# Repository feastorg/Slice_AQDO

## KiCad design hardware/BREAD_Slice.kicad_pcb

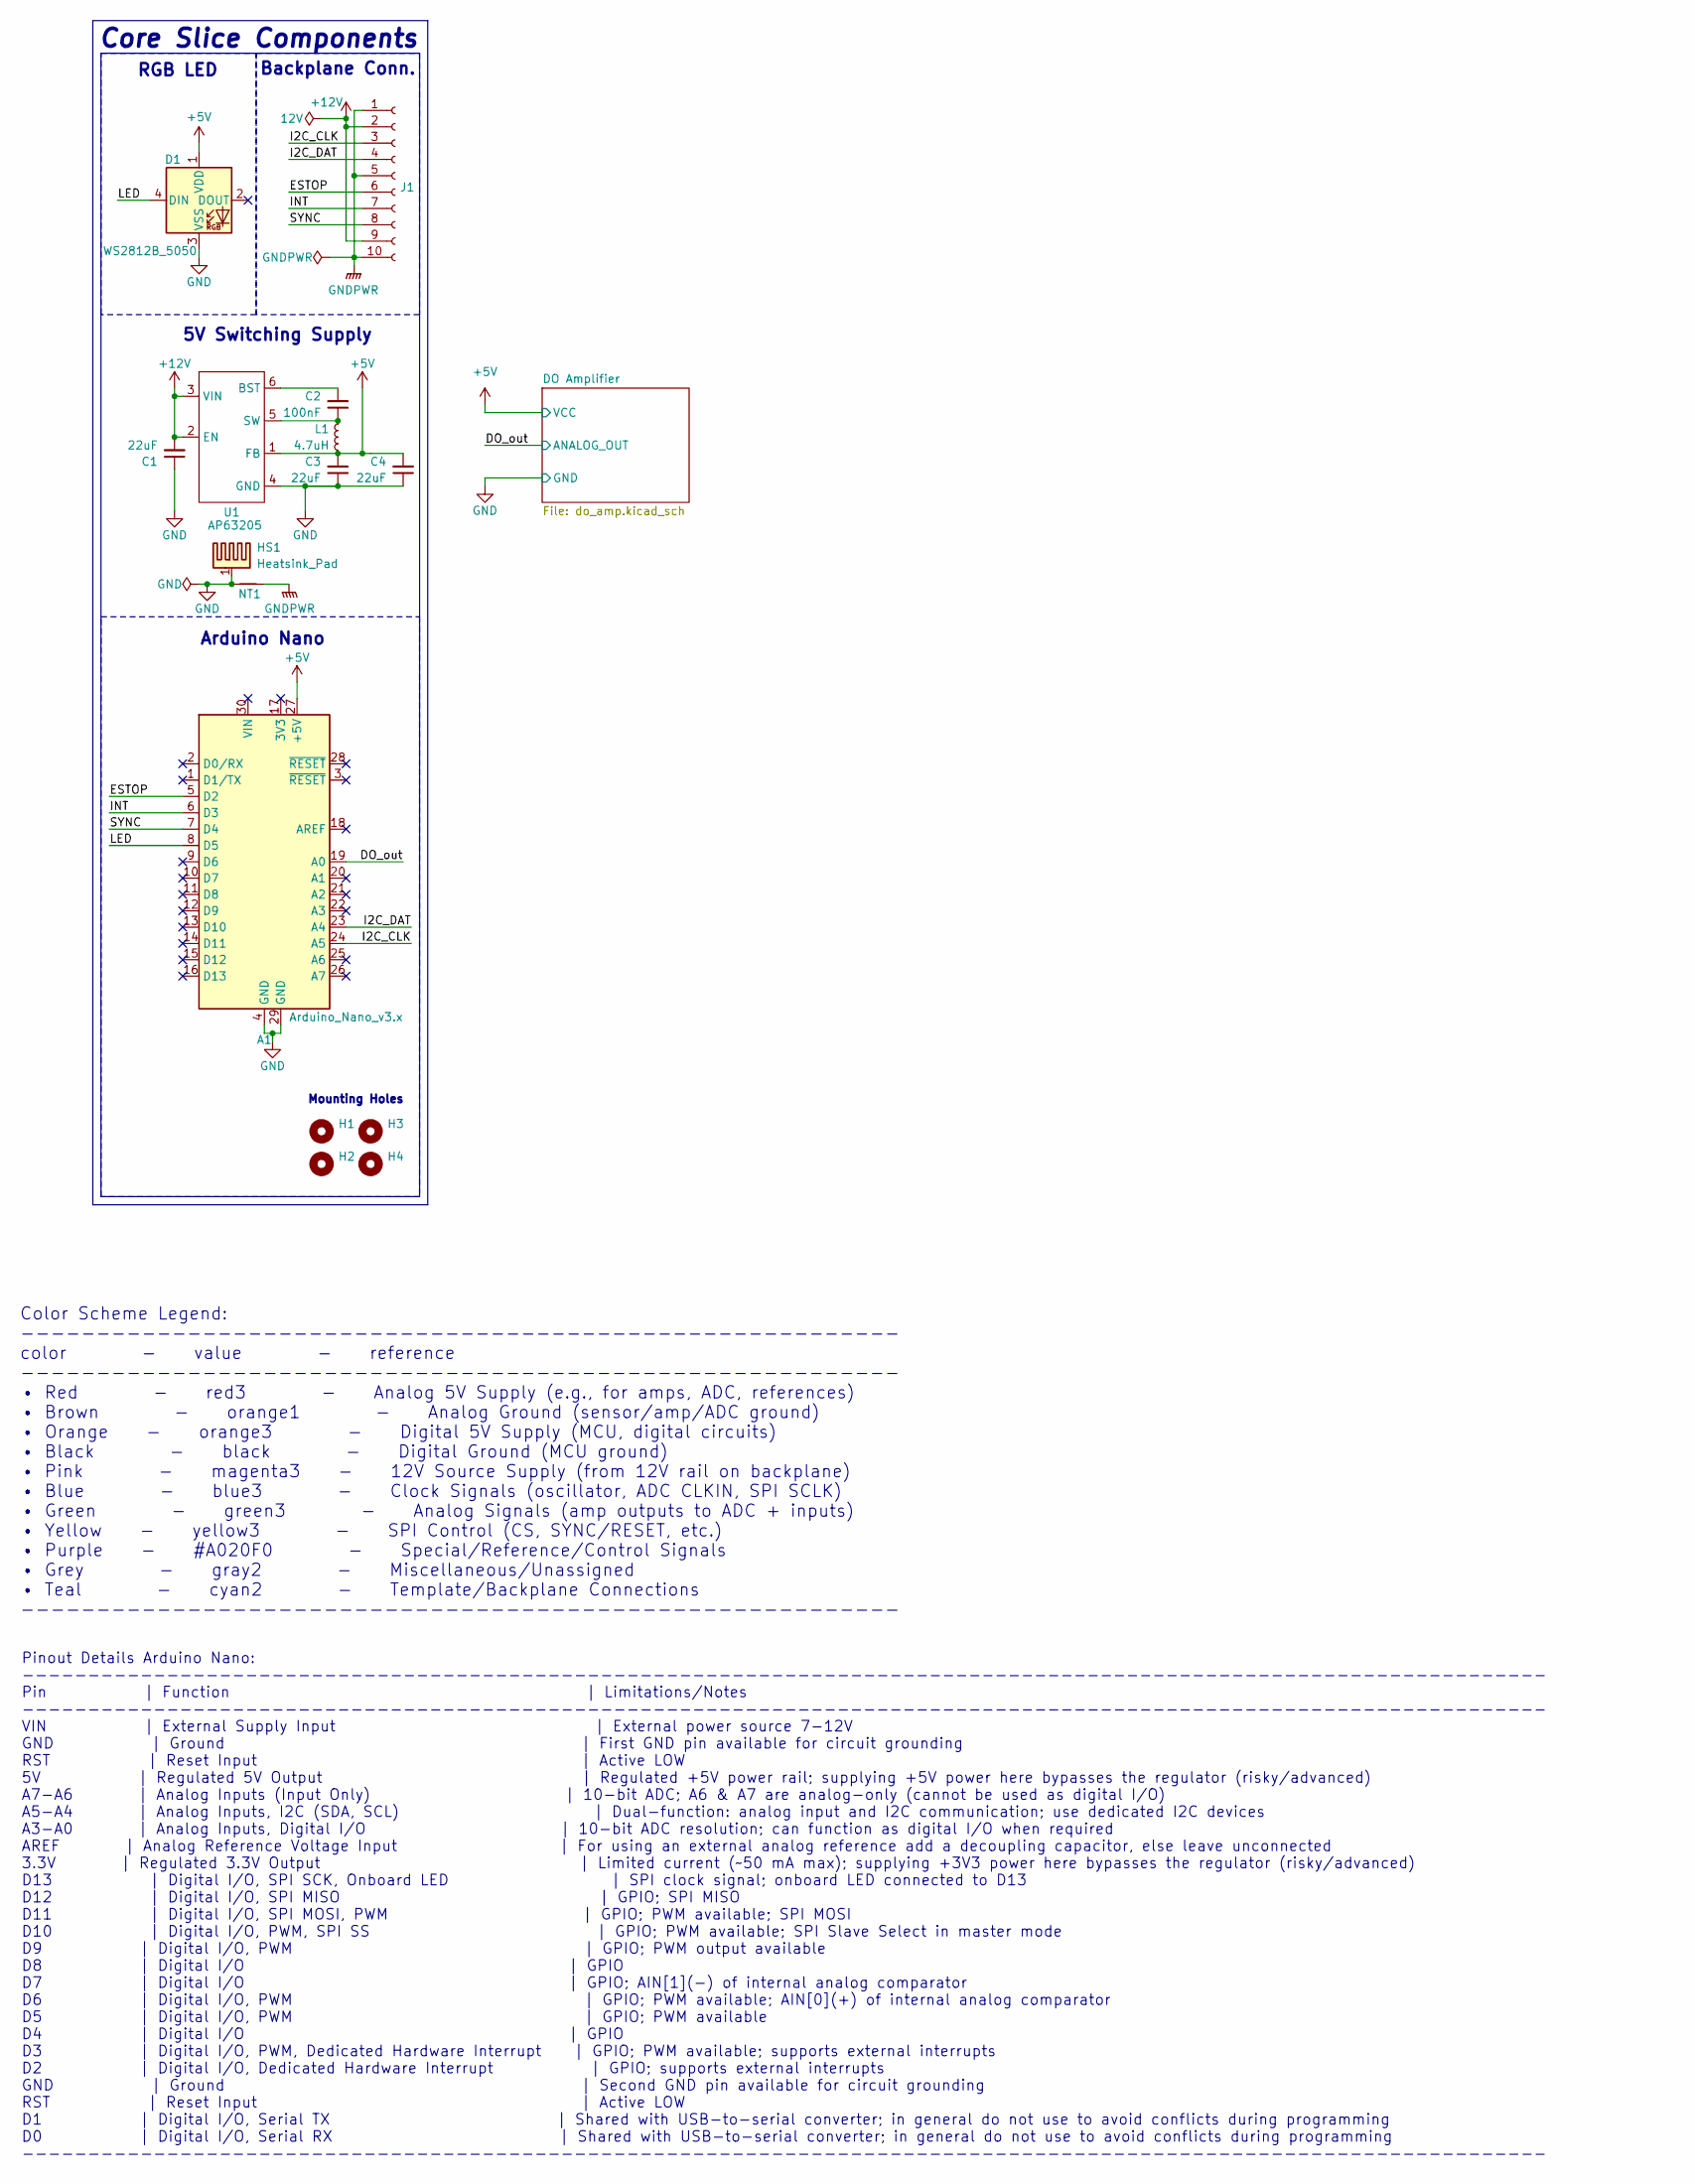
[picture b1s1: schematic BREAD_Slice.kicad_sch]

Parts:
A1: Arduino_Nano_v3.x; Arduino_Nano
C1, C3, C4: 22uF; C_1206_3216Metric
C2: 100nF; C_1206_3216Metric
D1: WS2812B_5050; WS2812-5050-4PIN
H1, H2, H3, H4: MountingHole; MountingHole_5mm
HS1: Heatsink_Pad; Thermal_Pad
J1: Conn_01x10_Female; PinSocket_1x10_P2.54mm_Horizontal
L1: 4.7uH; L_1210_3225Metric
NT1: NetTie_2; NetTie-2_SMD_Pad2.0mm
U1: AP63205; TSOT-23-6

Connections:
+5V: A1.27 (+5V), C3.2, C4.2, D1.1 (VDD), L1.2, U1.1 (FB); also elsewhere on the board
+12V: C1.2, J1.2, J1.9, U1.2 (EN), U1.3 (VIN)
/DO_out: A1.19 (A0); also elsewhere on the board
/ESTOP: A1.5 (D2), J1.6
/I2C_CLK: A1.24 (A5), J1.3
/I2C_DAT: A1.23 (A4), J1.4
/INT: A1.6 (D3), J1.7
/LED: A1.8 (D5), D1.4 (DIN)
/SYNC: A1.7 (D4), J1.8
GND: A1.4 (GND), A1.29 (GND), C1.1, C3.1, C4.1, D1.3 (VSS), HS1.1, NT1.1, U1.4 (GND); also elsewhere on the board
GNDPWR: J1.1, J1.5, J1.10, NT1.2
unnamed: C2.2, U1.6 (BST)
unnamed: C2.1, L1.1, U1.5 (SW)

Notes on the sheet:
5V Switching Supply
Pinout Details Arduino Nano: -------------------------------------------------------------------------------------------------------------------- Pin | Function | Limitations/Notes -------------------------------------------------------------------------------------------------------------------- V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
RGB LED
Color Scheme Legend: ---------------------------------------------------------- color - value - reference ---------------------------------------------------------- • Red - red3 - Analog 5V Supply (e.g., for amps, ADC, references) • Brown - orange1 - Analog Ground (sensor/amp/ADC ground) • Orange -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
Core Slice Components
Arduino Nano
Mounting Holes
Backplane Conn.

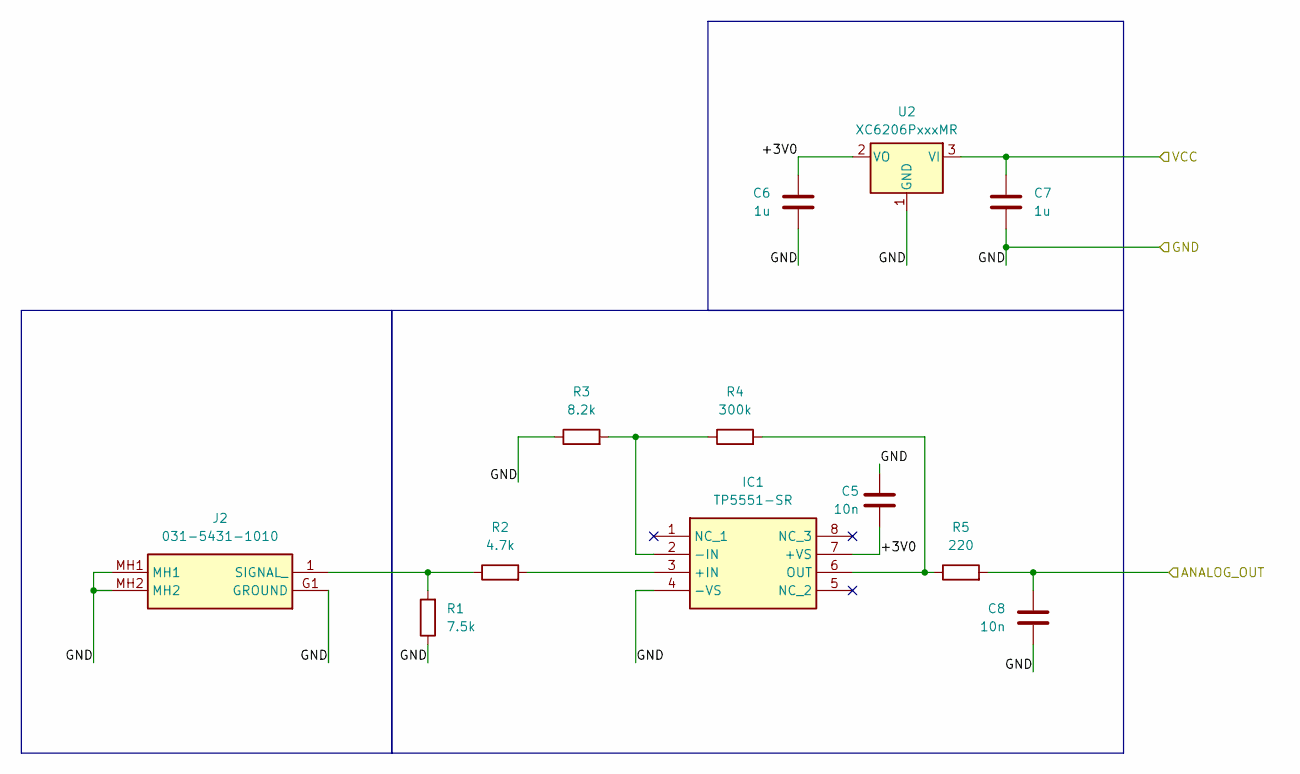
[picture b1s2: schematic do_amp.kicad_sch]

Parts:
C5, C8: 10n; C_0805_2012Metric_Pad1.18x1.45mm_HandSolder
C6, C7: 1u; C_0805_2012Metric_Pad1.18x1.45mm_HandSolder
IC1: TP5551-SR; SOIC127P600X175-8N; Manufacturer_Part_Number TP5551-SR
J2: 031-5431-1010; 03154311010; Mouser Part Number 523-31-5431-1010
R1: 7.5k; R_0805_2012Metric_Pad1.20x1.40mm_HandSolder
R2: 4.7k; R_0805_2012Metric_Pad1.20x1.40mm_HandSolder
R3: 8.2k; R_0805_2012Metric_Pad1.20x1.40mm_HandSolder
R4: 300k; R_0805_2012Metric_Pad1.20x1.40mm_HandSolder
R5: 220; R_0805_2012Metric_Pad1.20x1.40mm_HandSolder
U2: XC6206PxxxMR; SOT-23-3

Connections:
+5V: C7.1, U2.3 (VI); also elsewhere on the board
/DO Amplifier/+3V0: C5.2, C6.1, IC1.7 (+VS), U2.2 (VO)
/DO_out: C8.1, R5.2; also elsewhere on the board
GND: C5.1, C6.2, C7.2, C8.2, IC1.4 (-VS), J2.G1 (GROUND), J2.MH1, J2.MH2, R1.1, R3.1, U2.1 (GND); also elsewhere on the board
unnamed: IC1.3 (+IN), R2.2
unnamed: IC1.2 (-IN), R3.2, R4.1
unnamed: IC1.6 (OUT), R4.2, R5.1
unnamed: J2.1 (SIGNAL_), R1.2, R2.1

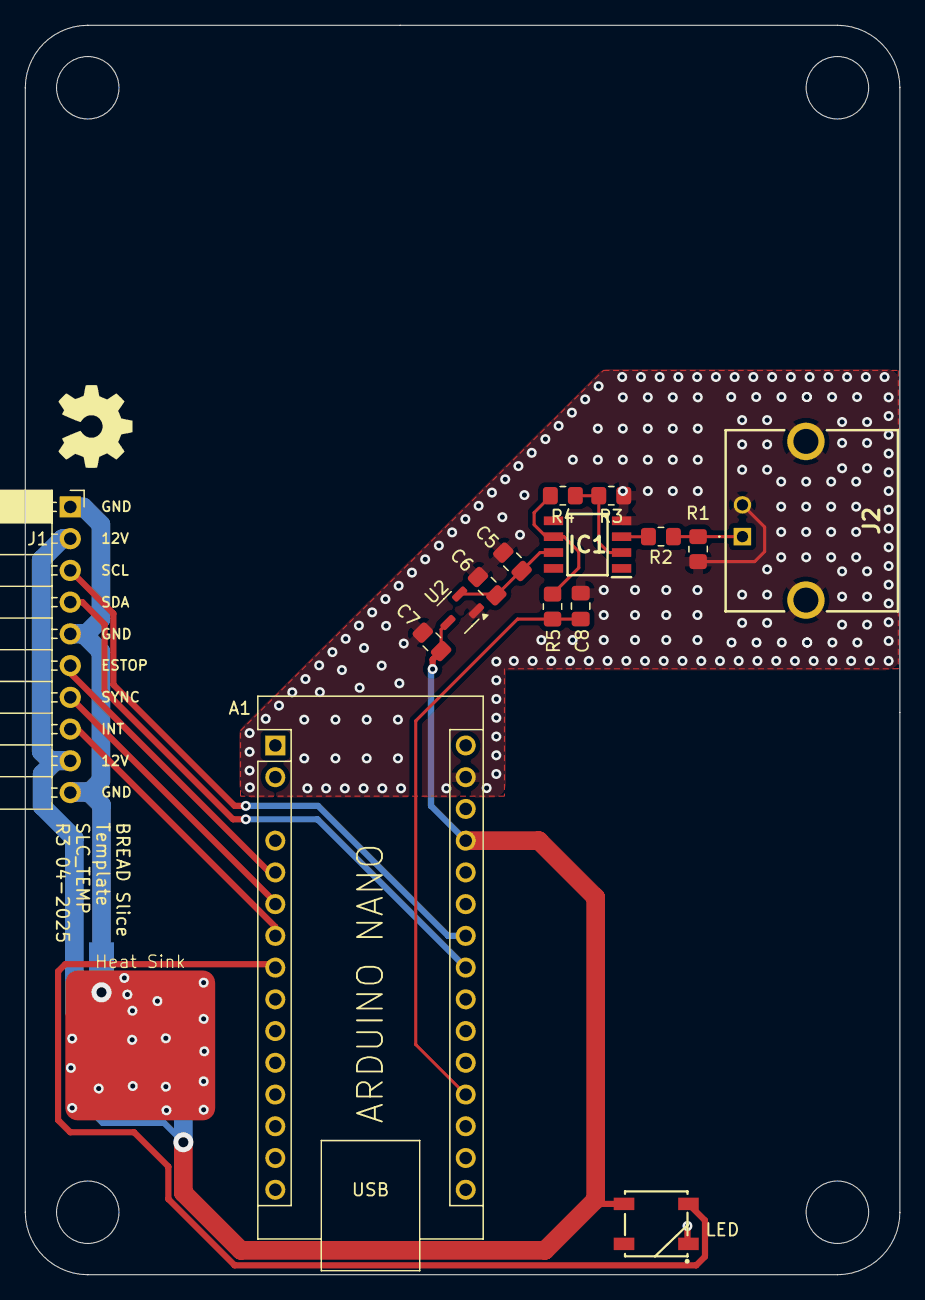
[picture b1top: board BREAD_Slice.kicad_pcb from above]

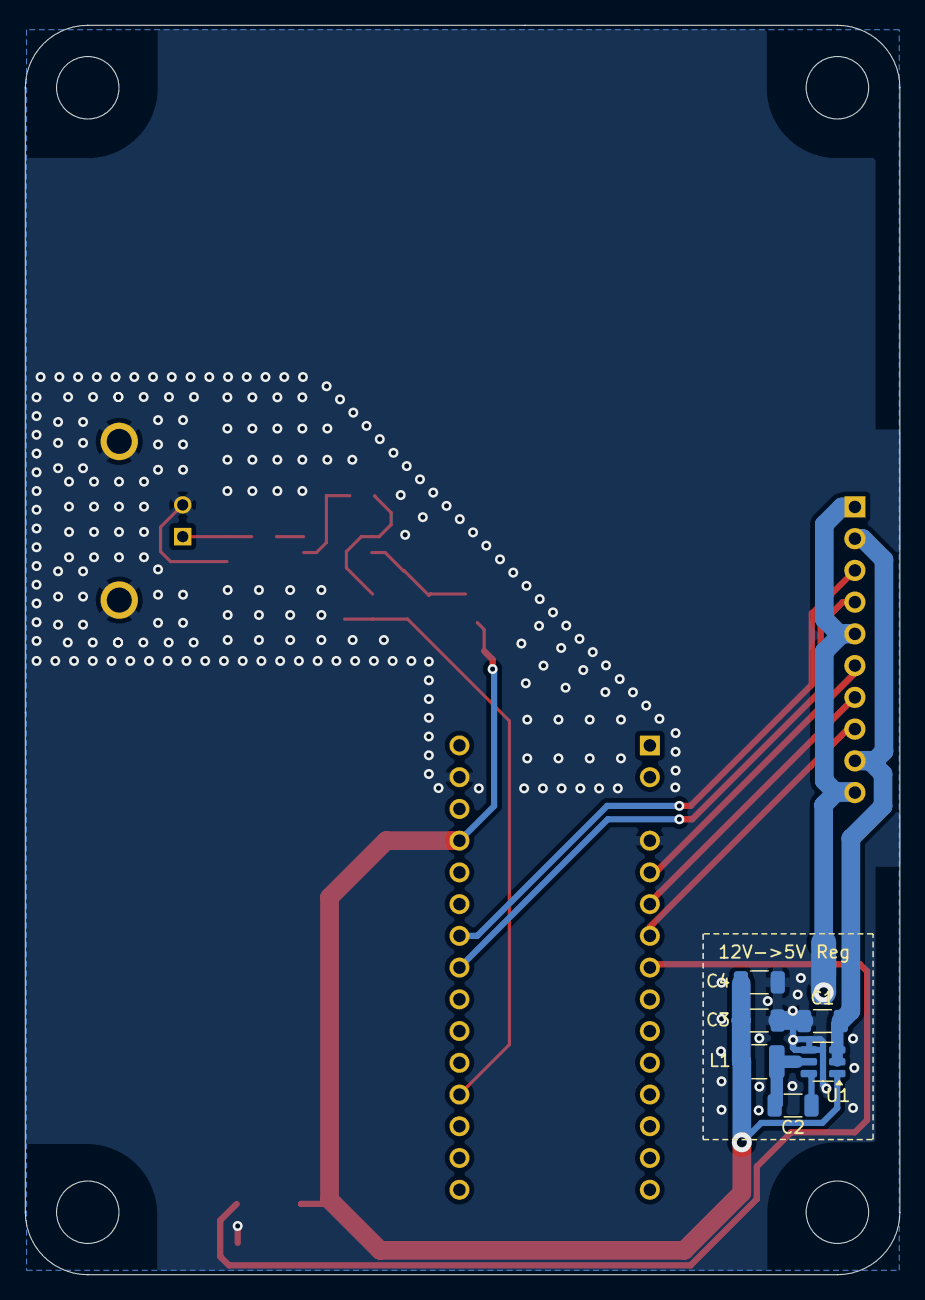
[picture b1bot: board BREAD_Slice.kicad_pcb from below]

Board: 2 copper layers, 70.0 x 100.0 mm, 28 parts (7 on the bottom side), 18 nets.

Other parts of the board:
Logo1: Logo_Open_Hardware_Small; OSHW-Symbol_6.7x6mm_SilkScreen

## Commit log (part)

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2025-04-17 updated docs
2025-04-19 minor tweaks
2026-04-18 chore: minor update
2026-05-20 Add slice.yaml manifest (schema v1.0)
2026-05-24 Add KiBot/docs pipeline
2026-05-24 📄 KiBot index + board renders (auto)
2026-05-24 Update TODO with CI results
2026-05-24 TODO: all CI green
